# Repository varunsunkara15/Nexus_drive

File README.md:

# Nexus Drive

**Nexus Drive** is an open-hardware motor driver we are designing for a humanoid robot's joints.

The goal is a compact board that can sit near each joint actuator and drive its motor accurately and efficiently. It should also report back to the robot's main controller.

> **Status:** 🚧 Early development. Schematic in progress (power stage, gate driver, MCU, CAN-FD, encoders and sensing drawn; ERC has 0 errors; logic supplies, DC-link and input protection still to add); PCB layout not started.

---

## Repository layout

```
Nexus_drive/
├── hardware/                     KiCad 10 project (open nexus_drive.kicad_pro)
│   ├── nexus_drive.kicad_pro     Project file
│   ├── nexus_drive.kicad_sch     Root schematic sheet
│   ├── gate_driver.kicad_sch     DRV8353S gate driver and support parts
│   ├── h_bridge.kicad_sch        One half-bridge (MOSFETs, shunt, phase output), used 3× for phases A/B/C
│   ├── current_sense.kicad_sch   RC filters on the current-sense amplifier outputs
│   ├── stm32g474.kicad_sch       STM32G474METx MCU, wired to the pin plan
│   ├── can_fd.kicad_sch          TCAN1042GV CAN-FD transceiver and bus connectors
│   ├── encoders.kicad_sch        On-board MA702GQ encoder and external SPI encoder connectors
│   ├── sensing.kicad_sch         Bus and phase voltage dividers, FET and motor temperature inputs
│   ├── nexus_drive.kicad_sym     Project symbols (TCAN1042GV, MA702GQ, EMI filter)
│   ├── nexus_drive.kicad_pcb     PCB layout (not started)
│   ├── fp-lib-table, sym-lib-table   Project library tables
│   └── lib/                      Project-local symbol and footprint libraries (moteus)
├── firmware/
│   └── Comms Component Selection.ioc   STM32CubeMX pin assignment for the MCU
├── docs/
│   └── power-stage.md            Power stage design notes
├── LICENSES/, NOTICE.md          Attribution for files derived from mjbots moteus (Apache-2.0)
└── README.md
```

Folders for fabrication outputs (Gerbers, BOM, pick-and-place) and datasheets will be added as the design matures.

## Design goals

These are the intended targets. Values still marked **TBD** will be filled in as we choose parts. The power stage is described in detail in [docs/power-stage.md](docs/power-stage.md).

- **Motor type:** Brushless DC / PMSM motors used in humanoid joint actuators
- **Control:** Field-oriented control (FOC) for smooth, quiet torque control
- **Feedback:** Rotor position sensing (e.g. a magnetic encoder) and phase current sensing
- **Communication:** A bus to the robot's main controller, such as CAN / CAN-FD
- **Protection:** Over-current, over-voltage, under-voltage and over-temperature protection
- **Form factor:** Small enough to mount on or inside the joint actuator

### Planned specifications

| Parameter | Target |
| --- | --- |
| Battery | 12S3P Li-ion / LiPo: 36–50.4 V (44–48 V nominal) |
| Continuous / peak phase current | TBD (depends on the motor) |
| Microcontroller | STM32G474METx (LQFP-80, 170 MHz Cortex-M4) |
| Gate driver | TI DRV8353S (SPI-configured, integrated current-sense amplifiers) |
| MOSFETs | 6 × onsemi FDMT80080DC (80 V, 1.35 mΩ) |
| Current sensing | 3 low-side shunts (value TBD) |
| Overvoltage protection | Input TVS, bulk capacitor, 100 V ceramic DC-link bank, anti-spark connector |
| Encoder interface | 3 × SPI: on-board MA702GQ magnetic encoder, 2 external connectors |
| Communication | CAN-FD (TCAN1042GV), two daisy-chain connectors |
| Board dimensions | TBD |

### Note: bulk capacitance on the battery bus

The power stage in this repo has **no bulk / DC-link capacitor bank yet**. It is owned by another team member and must be added before the board is built. The reference design (moteus x1) uses 36 × 4.7 µF 100 V ceramics. A **bulk electrolytic (or tantalum) capacitor** at the power input may also be needed. Reasons:

- **Hot-plug ringing:** a bank of only ceramics has very low ESR. Together with the battery cable's inductance, it can ring up to ~2× the battery voltage when the battery is plugged in (~100 V on a 50.4 V pack), above the 80 V MOSFET rating. An electrolytic's higher ESR (≈ 0.05–0.1 Ω) damps this ringing.
- **Ceramics lose capacitance under DC bias:** 100 V X7R ceramics keep only about 30–50 % of their rated value at 50 V, so the real bus capacitance is much lower than the printed value.
- **Regen and load steps:** a larger capacitor absorbs some regenerative braking energy and supplies current during fast load changes, reducing bus voltage swings.

Guidance: rated **80 V or higher** (63 V is the bare minimum), capacitance several times the effective ceramic bank (e.g. 330–470 µF total), ESR ≈ 0.05–0.1 Ω, placed between the input connector and the half-bridges. **Tantalum is not recommended at this voltage:** tantalums need ~2× voltage derating (a >100 V part is hard to find), and they tend to fail short-circuit, which is a fire risk on a stiff 12S3P pack. Aluminium electrolytic or hybrid polymer is the safer choice. See [docs/power-stage.md](docs/power-stage.md) for the full overvoltage-protection requirements.

## Schematic review (3 Nov 2026)

This review covers the schematic and the first PCB placement at commit `5195f6f`: footprint assignment, the HC-05 header on J1, footprint import, and the `sensing` sheet. It was checked against the KiCad netlist, ERC and DRC. Blocks that are still to be drawn (logic supplies, DC-link, input protection) are planned work and are not reviewed.

**Design intent: the board is deliberately over-specified.** The first target motors are the CubeMars **RO80 KV105** (≈15 A rated, ~50 A peak) and **RO100 KV55** (≈20 A rated, ~62 A peak) at 48 V. The power stage keeps moteus x1's 120 A-class parts so that larger motors can be used later.

**Checks:** ERC has 0 errors and 9 library warnings. PCB-to-schematic parity has 0 issues.

### ✅ Done well
- **All 115 parts have footprints, and the packages match the parts:** LQFP-80 for the STM32G474ME, RTA-40 for the DRV8353SRTA, PQFN 8×8 for the FETs, QFN-16 3×3 for the MA702 and SOIC-8 for the TCAN1042.
- **J1 (HC-05) is crossed over correctly:** MCU TX (PB10) goes to the module's RXD, and MCU RX (PE15) to its TXD.
- **The sensing sheet is well thought out:**
  - The VBUS divider (99.8k / 4.7k) gives 2.27 V at 50.4 V and reaches 3.3 V full scale at about 73 V, so it can see regen overvoltage.
  - The top resistor is split into two, so each 0603 sees only about 25 V.
  - The three phase-voltage dividers use the same ratio, filtered at about 3.5 kHz.
  - The thermistors have 1 % pull-ups and filter caps, and every signal goes to an ADC pin.
- Carried over from earlier work:
  - The power stage is copied from moteus x1 pin for pin.
  - DRV8353 nFAULT goes to TIM1_BKIN, so a driver fault stops PWM in hardware.
  - Each phase current has its own ADC.
  - CAN-FD has a choke, ESD protection and jumper-selectable termination.
  - Encoders have ESD protection and series resistors.

### 🔴 Fix before routing
- [ ] **N1: the VGLS capacitor C23 returns to `GND`.** VGLS supplies the low-side gate drive, so C23 must return to **`GNDPWR` at the DRV8353 PGND pin**. On `GND`, the gate current crosses between the two grounds every PWM cycle.
- [ ] **N2: `GND` and `GNDPWR` aren't joined anywhere.** NT1 joins only `GNDA` to `GND`, and NT3/5/7 are the shunt sense connections, so they don't count. Add **one net tie under the driver**.
- [ ] **N3: check FL1's pin numbers against the TDK ACT1210D datasheet.** The symbol uses windings 1–4 and 2–3. If TDK numbers them differently, the choke either shorts CANH to CANL or breaks the CAN line. Check the land pattern at the same time. Neither has been verified yet.
- [ ] **N4: placement has started before the parts that set the layout exist.** The DC-link capacitors, input connector and protection, and the logic supplies (+12 V, +5 V, +3.3 V) aren't drawn yet. Those decide where the power stage, the ground tie and the heat paths go. Finish them, plus N5, before placing parts seriously.

### 🟠 Should fix
- [ ] **N5: VM bulk capacitance.** +12 V (the DRV8353 VM pin) has only 0.1 µF (C19). Add the local bulk capacitor the DRV8353 datasheet recommends, next to the pin.
- [ ] **N6: drill size on the phase output pads.** X1–X3 each have 20 vias with 0.254 mm holes, but the board rule minimum is 0.3 mm, giving 60 DRC errors. Either confirm the fab can drill 0.25 mm and change the rule, or enlarge the holes to 0.3 mm. These vias carry phase current, so their size and count matter for the over-spec rating (N13).
- [ ] **N7: protect the motor thermistor input.** J7 leaves the board next to the phase wires and goes straight to the ADC with only 100 nF. Add about 1k in series and an ESD clamp. A motor thermistor sits inside the windings, so an insulation fault can put bus voltage on that ADC pin.
- [ ] **N8: HC-05 on J1.**
  - Nothing supplies `+5V` yet. Include the HC-05 (up to about 40 mA while pairing) and the TCAN1042 (about 70 mA) in the 5 V budget.
  - J1 is a male pin header and the HC-05 module also has male pins, so it needs a cable or a socket.
  - Treat Bluetooth as a bench and debug link only. CAN is the main bus for 12 joints.
- [ ] **N9: current-sense gain must be set per motor.** With the 0.5 mΩ shunts, gain 40 gives ±70 A full scale, for the RO80 and RO100. Gain 20 gives ±140 A, for larger motors. Make the gain a per-motor firmware parameter.
- [ ] **N10: gate-drive supply versus PWM frequency.** Six FDMT80080DC gates (195 nC each) at 30 kHz need about 35 mA. Check that against the DRV8353 charge-pump and VGLS limits before fixing the PWM frequency, and include it in the +12 V budget.
- [ ] **N11: sensing offset and ratiometric reference.** The current-sense amplifier zero (VREF/2) and the thermistor pull-ups run from `+3V`, but the ADC reference is `+3VA`. Calibrate the offsets at startup with the gates off, or move them to `+3VA`.
- [ ] **N12: external encoders.**
  - J903/J904 take power from the MCU's own `+3V`, so a shorted encoder cable resets the MCU. Add a polyfuse, a load switch or a separate LDO.
  - Keep single-ended SPI cables short and slow, or use RS-485/SSI for the joint-output encoder.
- [ ] **N13: thermal design for the over-spec rating.** The 120 A-class headroom only holds with:
  - heavy copper for V+, the phases and `GNDPWR`
  - a thermal path for the Dual Cool FETs
  - shunts sized for the largest motor you plan to use

### 🟡 Housekeeping
- [ ] **N14:** `sym-lib-table` has no `nexus_drive` entry, which causes 3 ERC warnings.
- [ ] **N15:** The U6 footprint differs from the library copy. Update it from the library, or note why it's custom.
- [ ] **N16:** Before routing, add the board outline. The 196 silkscreen warnings from placement can be cleaned up later.
- [ ] **N17:** Check the following:
  - The SWD header order (VCC, SWDIO, SWCLK, NRST, GND) isn't a standard pinout. Match it to your programmer.
  - The 12 pF crystal caps should suit the 16 MHz crystal's load capacitance.
  - PD10 (DRV chip select) has no label in the `.ioc`.
- [ ] **N18:** Consider split CAN termination (2 × 60 Ω + ~4.7 nF to GND) for better EMC on a long robot bus.
- [ ] **N19:** Commit the literature review (moteus, ODrive, ODESC, ODRI) to `docs/`.

**Most important:** N1, N2 and N4. Get the grounding and the missing power blocks into the schematic before routing.

## Getting started

### Requirements

- [KiCad](https://www.kicad.org/) **10.0** or newer. The project files use the KiCad 10 format and will not open in older versions.

### Opening the project

```bash
git clone https://github.com/varunsunkara15/Nexus_drive.git
cd Nexus_drive
```

Then open `hardware/nexus_drive.kicad_pro` in KiCad.

## Roadmap

- [x] Create the KiCad project and repository
- [ ] Define the specifications (battery voltage ✅, motor current, motor type)
- [ ] Choose the main parts (gate driver ✅, MOSFETs ✅, MCU ✅, shunts, encoder)
- [ ] Draw the schematic (phase power section ✅, gate driver ✅, MCU pin connections ✅, CAN-FD ✅, encoders ✅, sensing ✅, logic supplies, DC-link, input protection)
- [ ] Lay out the PCB
- [ ] Run design review, DRC and ERC
- [ ] Order and assemble the first prototype
- [ ] Bring up the board and write the firmware (FOC loop, communication)
- [ ] Test on a humanoid joint actuator

## Contributing

This project is under active development. Issues and pull requests are welcome. Please describe the change you're proposing, and why, before sending large design changes.

## License

No license has been chosen yet. Until one is added, all rights are reserved by the authors.

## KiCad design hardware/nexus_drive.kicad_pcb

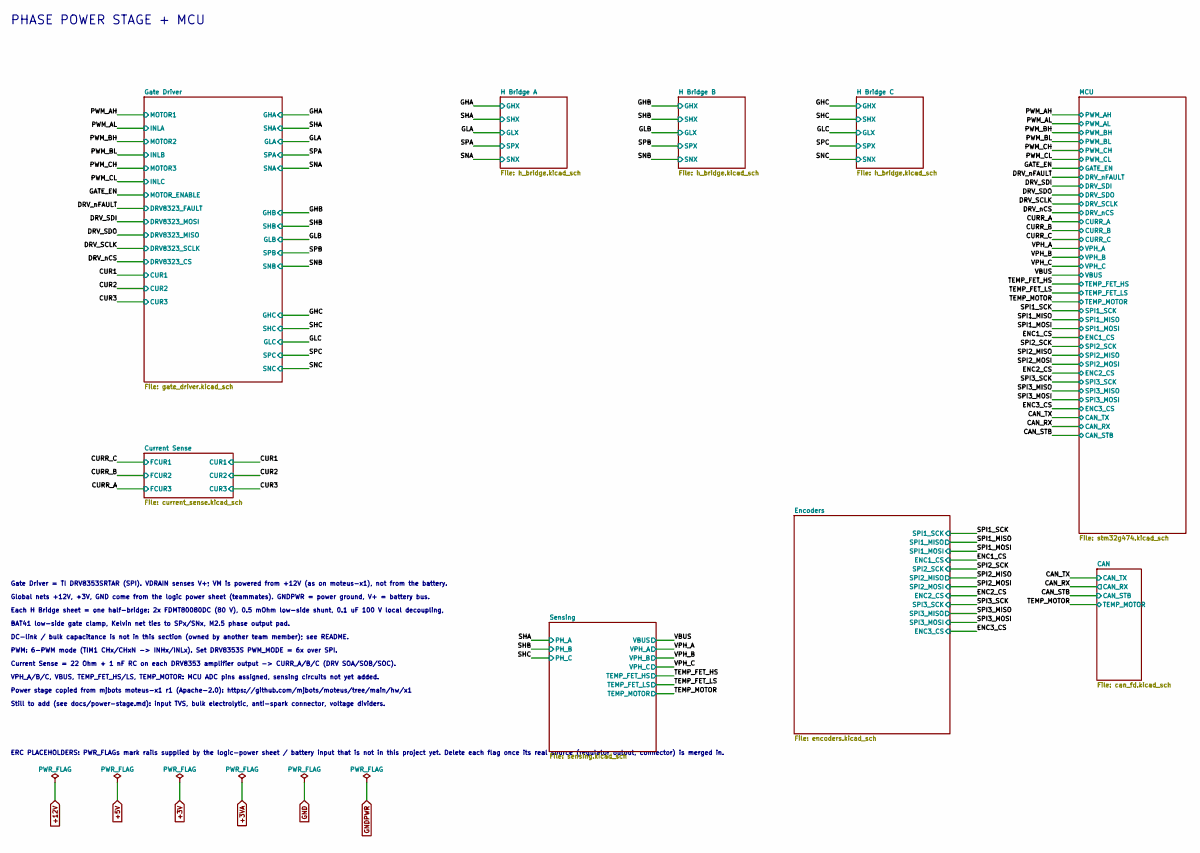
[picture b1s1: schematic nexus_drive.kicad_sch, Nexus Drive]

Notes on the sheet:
PWM: 6-PWM mode (TIM1 CHx/CHxN -> INHx/INLx). Set DRV8353S PWM_MODE = 6x over SPI.
Each H Bridge sheet = one half-bridge: 2x FDMT80080DC (80 V), 0.5 mOhm low-side shunt, 0.1 uF 100 V local decoupling,
Global nets +12V, +3V, GND come from the logic power sheet (teammates). GNDPWR = power ground, V+ = battery bus.
Gate Driver = TI DRV8353SRTAR (SPI). VDRAIN senses V+; VM is powered from +12V (as on moteus-x1), not from the battery.
DC-link / bulk capacitance is not in this section (owned by another team member); see README.
BAT41 low-side gate clamp, Kelvin net ties to SPx/SNx, M2.5 phase output pad.
Power stage copied from mjbots moteus-x1 r1 (Apache-2.0): https://github.com/mjbots/moteus/tree/main/hw/x1
Current Sense = 22 Ohm + 1 nF RC on each DRV8353 amplifier output -> CURR_A/B/C (DRV SOA/SOB/SOC).
ERC PLACEHOLDERS: PWR_FLAGs mark rails supplied by the logic-power sheet / battery input that is not in this project yet. Delete each flag once its real source (regulator output, connector) is merged in.
PHASE POWER STAGE + MCU
VPH_A/B/C, VBUS, TEMP_FET_HS/LS, TEMP_MOTOR: MCU ADC pins assigned, sensing circuits not yet added.
Still to add (see docs/power-stage.md): input TVS, bulk electrolytic, anti-spark connector, voltage dividers.

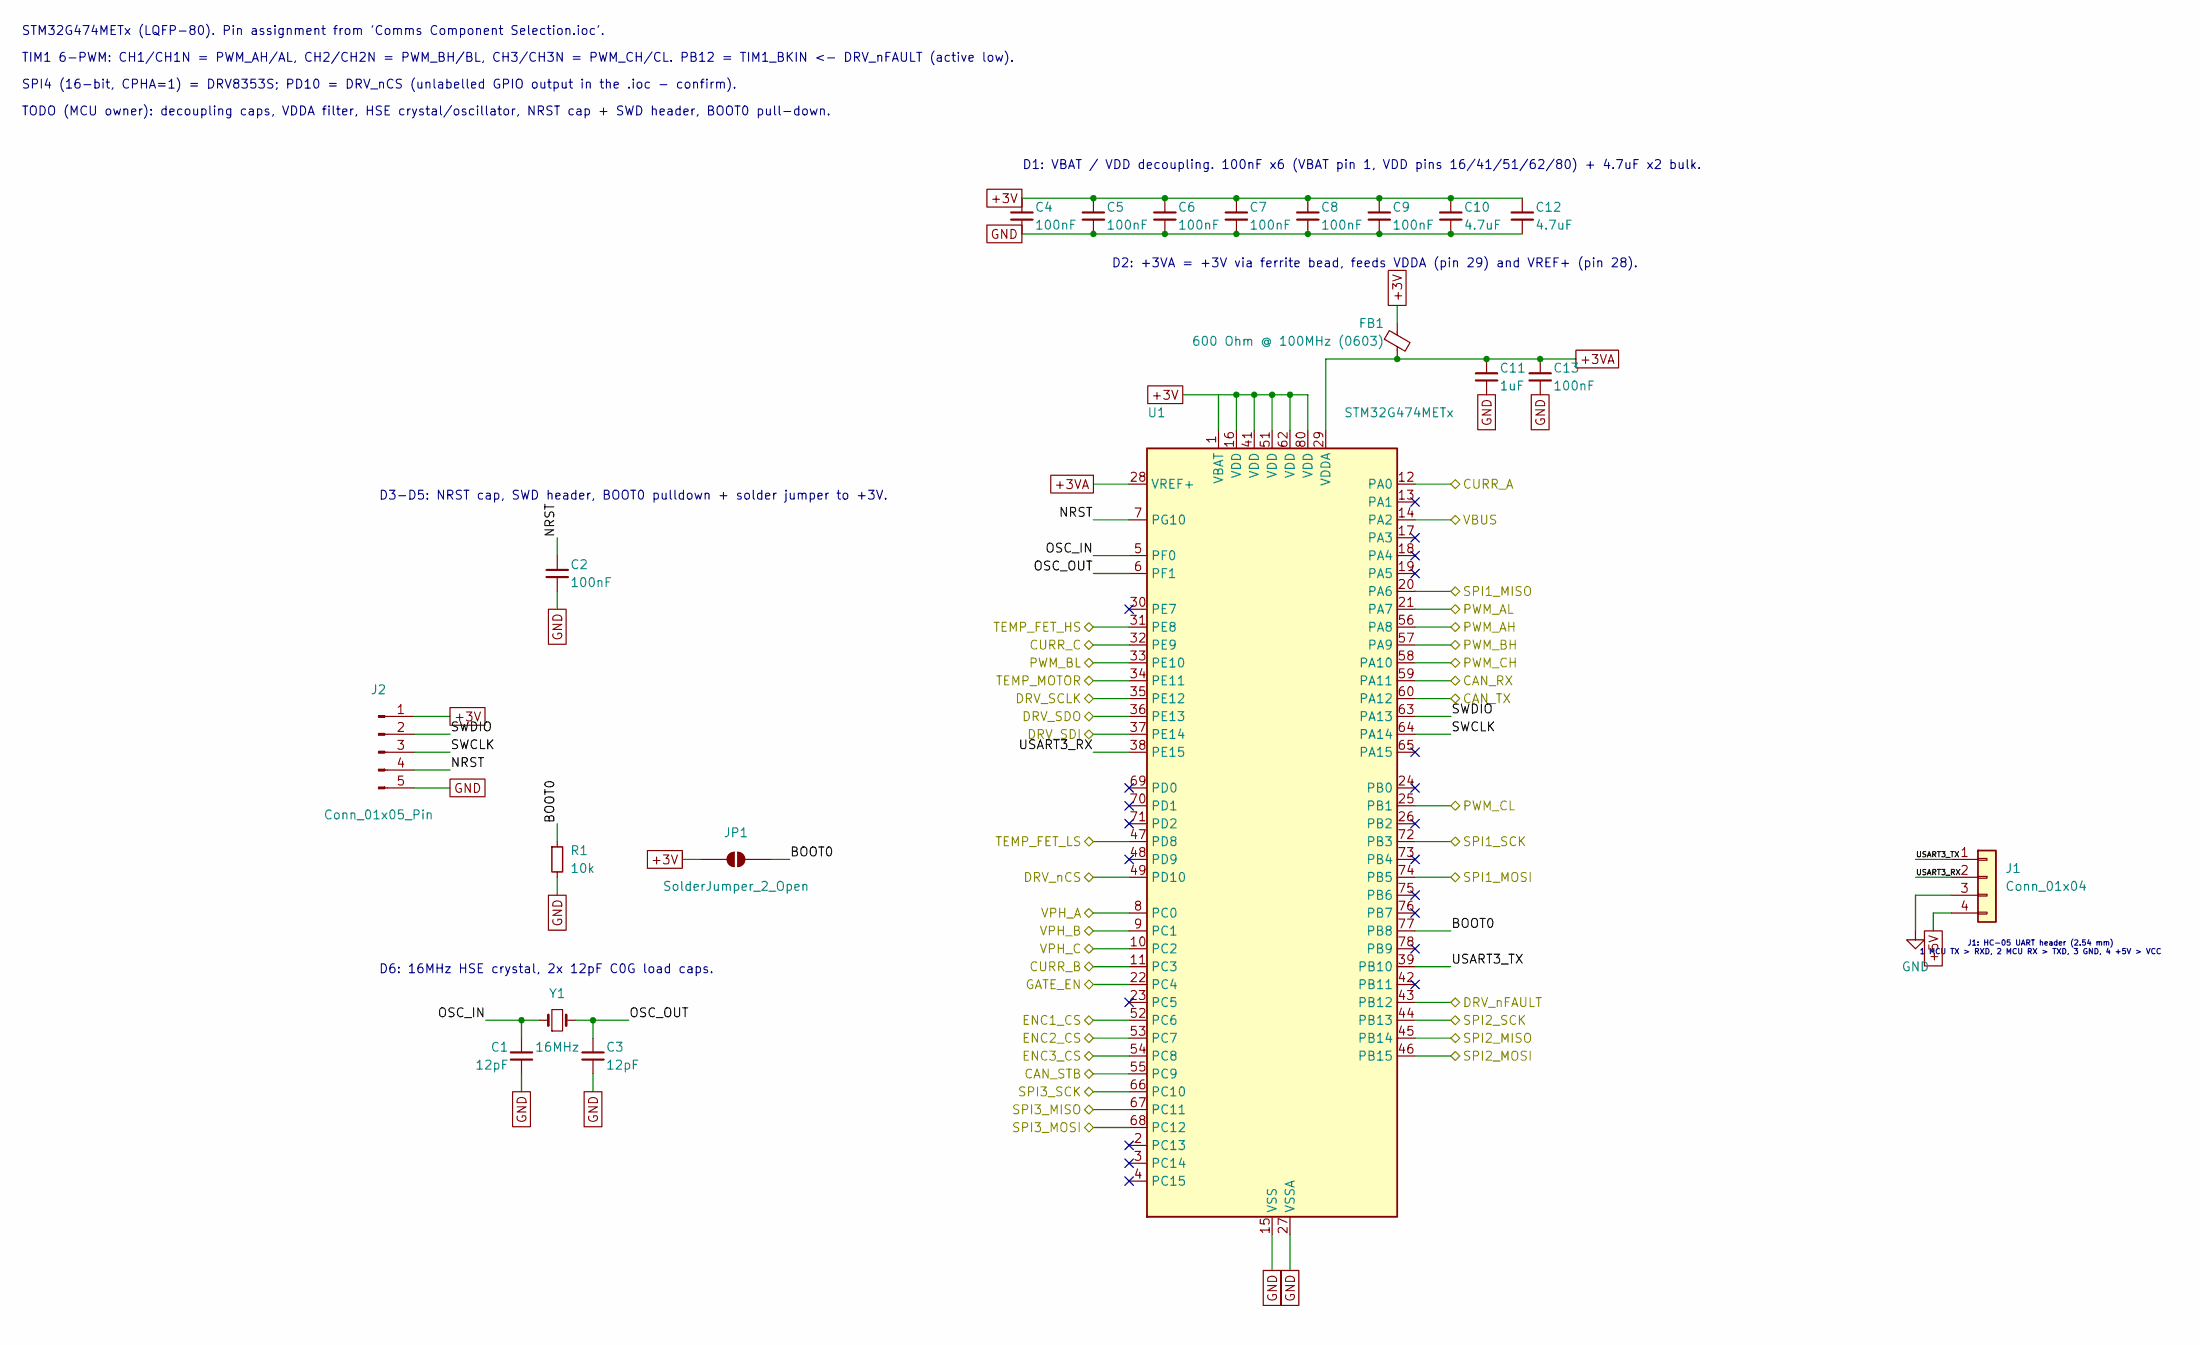
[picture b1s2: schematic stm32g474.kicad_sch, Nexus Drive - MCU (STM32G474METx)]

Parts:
C1, C3: 12pF; C_0603_1608Metric
C2, C4, C5, C6, C7, C8, C9, C13: 100nF; C_0603_1608Metric
C10, C12: 4.7uF; C_0805_2012Metric
C11: 1uF; C_0603_1608Metric
FB1: 600 Ohm @ 100MHz (0603); L_0603_1608Metric
J1: Conn_01x04; PinHeader_1x04_P2.54mm_Vertical
J2: Conn_01x05_Pin; PinHeader_1x05_P1.27mm_Vertical
JP1: SolderJumper_2_Open; SolderJumper-2_P1.3mm_Open_Pad1.0x1.5mm
R1: 10k; R_0603_1608Metric
U1: STM32G474METx; LQFP-80_12x12mm_P0.5mm
Y1: 16MHz; Crystal_SMD_5032-2Pin_5.0x3.2mm; MPN ABM8-16.000MHZ-10-1-U-T

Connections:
+3V: C4.1, C5.1, C6.1, C7.1, C8.1, C9.1, C10.1, C12.1, FB1.1, J2.1, JP1.1 (A), U1.1 (VBAT), U1.16 (VDD), U1.41 (VDD), U1.51 (VDD), U1.62 (VDD), U1.80 (VDD); also elsewhere on the board
+3VA: C11.1, C13.1, FB1.2, U1.28 (VREF+), U1.29 (VDDA); also elsewhere on the board
+5V: J1.4; also elsewhere on the board
/CAN_RX: U1.59 (PA11); also elsewhere on the board
/CAN_STB: U1.55 (PC9); also elsewhere on the board
/CAN_TX: U1.60 (PA12); also elsewhere on the board
/CURR_A: U1.12 (PA0); also elsewhere on the board
/CURR_B: U1.11 (PC3); also elsewhere on the board
/CURR_C: U1.32 (PE9); also elsewhere on the board
/DRV_SCLK: U1.35 (PE12); also elsewhere on the board
/DRV_SDI: U1.37 (PE14); also elsewhere on the board
/DRV_SDO: U1.36 (PE13); also elsewhere on the board
/DRV_nCS: U1.49 (PD10); also elsewhere on the board
/DRV_nFAULT: U1.43 (PB12); also elsewhere on the board
/ENC1_CS: U1.52 (PC6); also elsewhere on the board
/ENC2_CS: U1.53 (PC7); also elsewhere on the board
/ENC3_CS: U1.54 (PC8); also elsewhere on the board
/GATE_EN: U1.22 (PC4); also elsewhere on the board
/MCU/BOOT0: JP1.2 (B), R1.1, U1.77 (PB8)
/MCU/NRST: C2.1, J2.4, U1.7 (PG10)
/MCU/OSC_IN: C1.1, U1.5 (PF0), Y1.1
/MCU/OSC_OUT: C3.1, U1.6 (PF1), Y1.2
/MCU/SWCLK: J2.3, U1.64 (PA14)
/MCU/SWDIO: J2.2, U1.63 (PA13)
/MCU/USART3_RX: J1.2, U1.38 (PE15)
/MCU/USART3_TX: J1.1, U1.39 (PB10)
/PWM_AH: U1.56 (PA8); also elsewhere on the board
/PWM_AL: U1.21 (PA7); also elsewhere on the board
/PWM_BH: U1.57 (PA9); also elsewhere on the board
/PWM_BL: U1.33 (PE10); also elsewhere on the board
/PWM_CH: U1.58 (PA10); also elsewhere on the board
/PWM_CL: U1.25 (PB1); also elsewhere on the board
/SPI1_MISO: U1.20 (PA6); also elsewhere on the board
/SPI1_MOSI: U1.74 (PB5); also elsewhere on the board
/SPI1_SCK: U1.72 (PB3); also elsewhere on the board
/SPI2_MISO: U1.45 (PB14); also elsewhere on the board
/SPI2_MOSI: U1.46 (PB15); also elsewhere on the board
/SPI2_SCK: U1.44 (PB13); also elsewhere on the board
/SPI3_MISO: U1.67 (PC11); also elsewhere on the board
/SPI3_MOSI: U1.68 (PC12); also elsewhere on the board
/SPI3_SCK: U1.66 (PC10); also elsewhere on the board
/TEMP_FET_HS: U1.31 (PE8); also elsewhere on the board
/TEMP_FET_LS: U1.47 (PD8); also elsewhere on the board
/TEMP_MOTOR: U1.34 (PE11); also elsewhere on the board
/VBUS: U1.14 (PA2); also elsewhere on the board
/VPH_A: U1.8 (PC0); also elsewhere on the board
/VPH_B: U1.9 (PC1); also elsewhere on the board
/VPH_C: U1.10 (PC2); also elsewhere on the board
GND: C1.2, C2.2, C3.2, C4.2, C5.2, C6.2, C7.2, C8.2, C9.2, C10.2, C11.2, C12.2, C13.2, J1.3, J2.5, R1.2, U1.15 (VSS), U1.27 (VSSA), U1.40 (VSS), U1.50 (VSS), U1.61 (VSS), U1.79 (VSS); also elsewhere on the board

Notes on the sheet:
D2: +3VA = +3V via ferrite bead, feeds VDDA (pin 29) and VREF+ (pin 28).
J1: HC-05 UART header (2.54 mm) 1 MCU TX > RXD, 2 MCU RX > TXD, 3 GND, 4 +5V > VCC
TODO (MCU owner): decoupling caps, VDDA filter, HSE crystal/oscillator, NRST cap + SWD header, BOOT0 pull-down.
SPI4 (16-bit, CPHA=1) = DRV8353S; PD10 = DRV_nCS (unlabelled GPIO output in the .ioc - confirm).
D1: VBAT / VDD decoupling. 100nF x6 (VBAT pin 1, VDD pins 16/41/51/62/80) + 4.7uF x2 bulk.
D6: 16MHz HSE crystal, 2x 12pF C0G load caps.
STM32G474METx (LQFP-80). Pin assignment from 'Comms Component Selection.ioc'.
TIM1 6-PWM: CH1/CH1N = PWM_AH/AL, CH2/CH2N = PWM_BH/BL, CH3/CH3N = PWM_CH/CL. PB12 = TIM1_BKIN <- DRV_nFAULT (active low).
D3-D5: NRST cap, SWD header, BOOT0 pulldown + solder jumper to +3V.

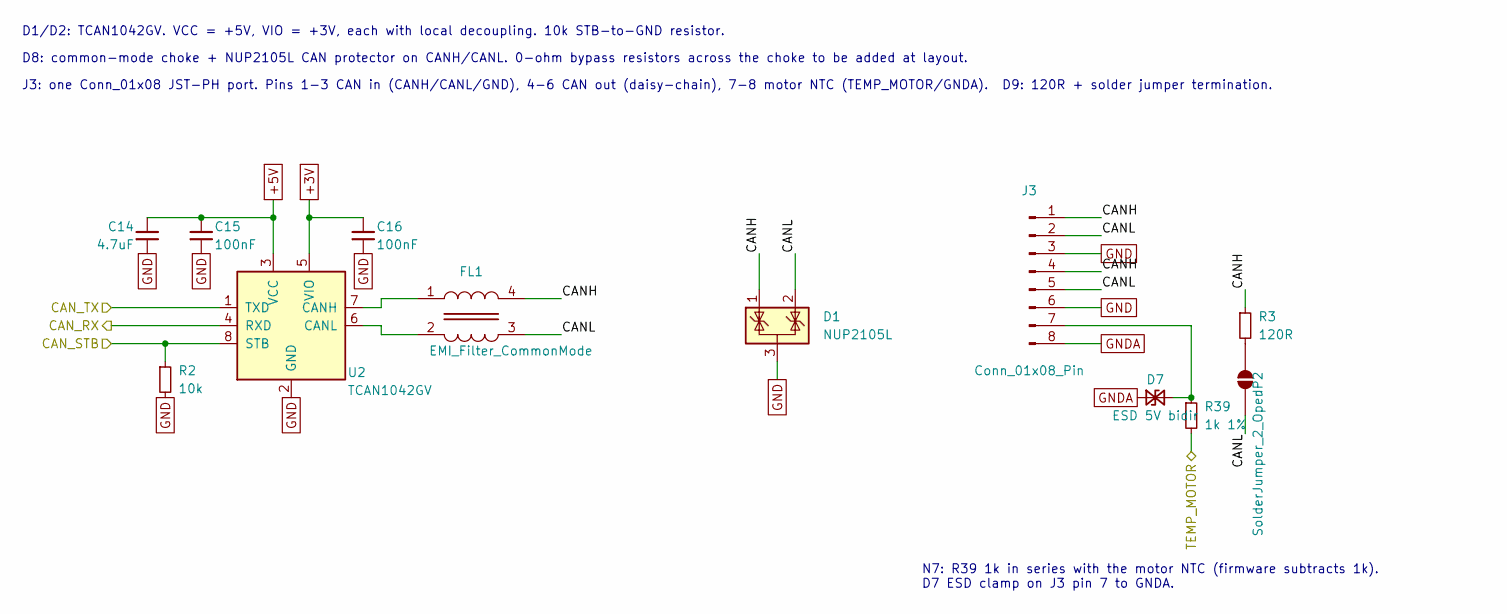
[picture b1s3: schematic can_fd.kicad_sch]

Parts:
C14: 4.7uF; C_0805_2012Metric
C15, C16: 100nF; C_0603_1608Metric
D1: NUP2105L; SOT-23
D7: ESD 5V bidir; D_SOD-323
FL1: EMI_Filter_CommonMode; L_CommonMode_TDK_ACT1210D
J3: Conn_01x08_Pin; JST_PH_B8B-PH-K_1x08_P2.00mm_Vertical
JP2: SolderJumper_2_Open; SolderJumper-2_P1.3mm_Open_Pad1.0x1.5mm
R2: 10k; R_0603_1608Metric
R3: 120R; R_0603_1608Metric
R39: 1k 1%; R_0603_1608Metric
U2: TCAN1042GV; SOIC-8_3.9x4.9mm_P1.27mm

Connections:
+3V: C16.1, U2.5 (VIO); also elsewhere on the board
+5V: C14.1, C15.1, U2.3 (VCC); also elsewhere on the board
/CAN/CANH: D1.1 (K), FL1.4, J3.1, J3.4, R3.1
/CAN/CANL: D1.2 (K), FL1.3, J3.2, J3.5, JP2.2 (B)
/CAN_RX: U2.4 (RXD); also elsewhere on the board
/CAN_STB: R2.1, U2.8 (STB); also elsewhere on the board
/CAN_TX: U2.1 (TXD); also elsewhere on the board
/TEMP_MOTOR: R39.2; also elsewhere on the board
GND: C14.2, C15.2, C16.2, D1.3 (A), J3.3, J3.6, R2.2, U2.2 (GND); also elsewhere on the board
GNDA: D7.1 (A1), J3.8; also elsewhere on the board
unnamed: D7.2 (A2), J3.7, R39.1
unnamed: JP2.1 (A), R3.2
unnamed: FL1.1, U2.7 (CANH)
unnamed: FL1.2, U2.6 (CANL)

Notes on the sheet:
D8: common-mode choke + NUP2105L CAN protector on CANH/CANL. 0-ohm bypass resistors across the choke to be added at layout.
D1/D2: TCAN1042GV. VCC = +5V, VIO = +3V, each with local decoupling. 10k STB-to-GND resistor.
J3: one Conn_01x08 JST-PH port. Pins 1-3 CAN in (CANH/CANL/GND), 4-6 CAN out (daisy-chain), 7-8 motor NTC (TEMP_MOTOR/GNDA). D9: 120R + solder jumper termination.
N7: R39 1k in series with the motor NTC (firmware subtracts 1k). D7 ESD clamp on J3 pin 7 to GNDA.

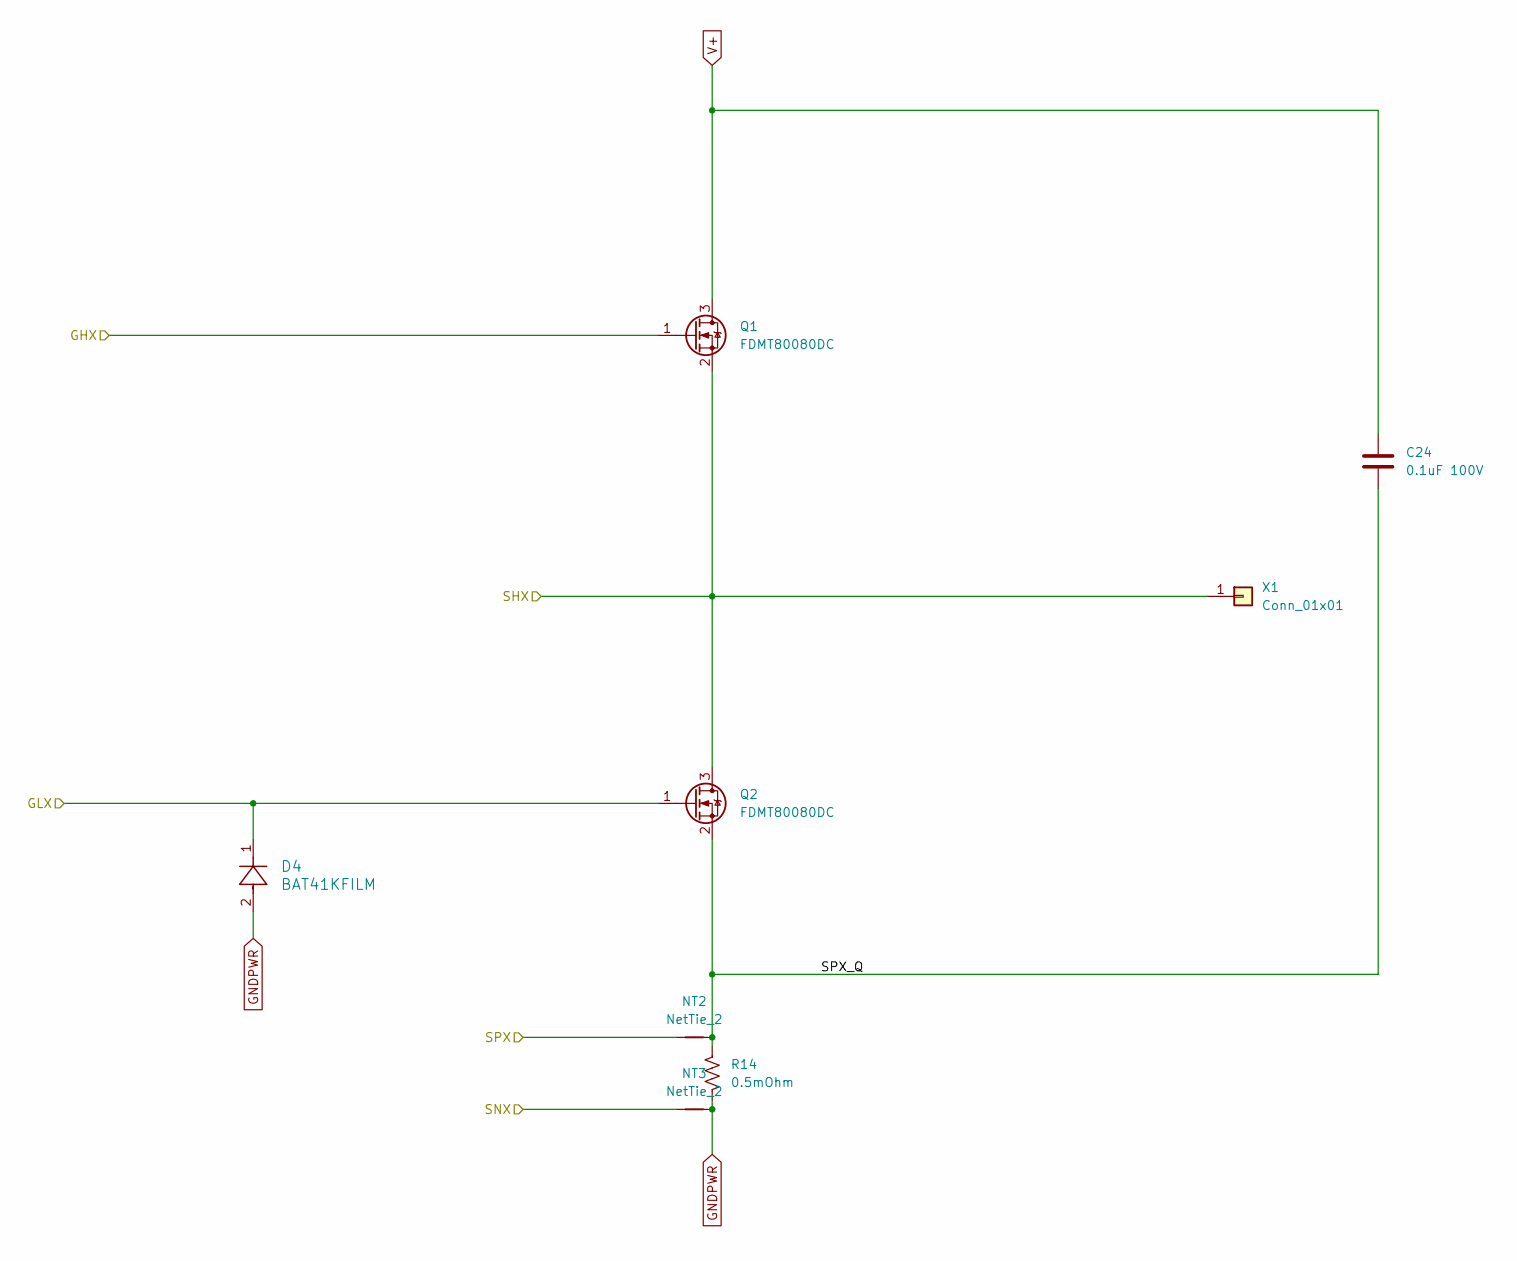
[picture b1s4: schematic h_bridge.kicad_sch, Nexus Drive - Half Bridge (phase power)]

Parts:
C24: 0.1uF 100V; C_1812_4532Metric; MPN 18121C104MAT2A
D4: BAT41KFILM; SOD-523_STM; MPN BAT41KFILM
NT2, NT3: NetTie_2; NetTie-2_SMD_Pad0.2
Q1, Q2: FDMT80080DC; PQFN_8x8; MPN FDMT80080DC
R14: 0.5mOhm; R_2512_6332Metric; MPN WSLF2512L5000FEA
X1: Conn_01x01; POWER_M2.5

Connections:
/GHA: Q1.1 (G); also elsewhere on the board
/GLA: D4.1, Q2.1 (G); also elsewhere on the board
/H Bridge A/SPX_Q: C24.2, NT2.2, Q2.2 (S), R14.1
/SHA: Q1.2 (S), Q2.3 (D), X1.1 (Pin_1_1); also elsewhere on the board
/SNA: NT3.1; also elsewhere on the board
/SPA: NT2.1; also elsewhere on the board
GNDPWR: D4.2, NT3.2, R14.2; also elsewhere on the board
V+: C24.1, Q1.3 (D); also elsewhere on the board

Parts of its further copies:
C25, C26: 0.1uF 100V; C_1812_4532Metric; MPN 18121C104MAT2A
D5, D6: BAT41KFILM; SOD-523_STM; MPN BAT41KFILM
NT4, NT5, NT6, NT7: NetTie_2; NetTie-2_SMD_Pad0.2
Q3, Q4, Q5, Q6: FDMT80080DC; PQFN_8x8; MPN FDMT80080DC
R15, R16: 0.5mOhm; R_2512_6332Metric; MPN WSLF2512L5000FEA
X2, X3: Conn_01x01; POWER_M2.5

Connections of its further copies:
/GHB: Q3.1 (G); also elsewhere on the board
/GHC: Q5.1 (G); also elsewhere on the board
/GLB: D5.1, Q4.1 (G); also elsewhere on the board
/GLC: D6.1, Q6.1 (G); also elsewhere on the board
/H Bridge B/SPX_Q: C25.2, NT4.2, Q4.2 (S), R15.1
/H Bridge C/SPX_Q: C26.2, NT6.2, Q6.2 (S), R16.1
/SHB: Q3.2 (S), Q4.3 (D), X2.1 (Pin_1_1); also elsewhere on the board
/SHC: Q5.2 (S), Q6.3 (D), X3.1 (Pin_1_1); also elsewhere on the board
/SNB: NT5.1; also elsewhere on the board
/SNC: NT7.1; also elsewhere on the board
/SPB: NT4.1; also elsewhere on the board
/SPC: NT6.1; also elsewhere on the board
GNDPWR: D5.2, D6.2, NT5.2, NT7.2, R15.2, R16.2; also elsewhere on the board
V+: C25.1, C26.1, Q3.3 (D), Q5.3 (D); also elsewhere on the board

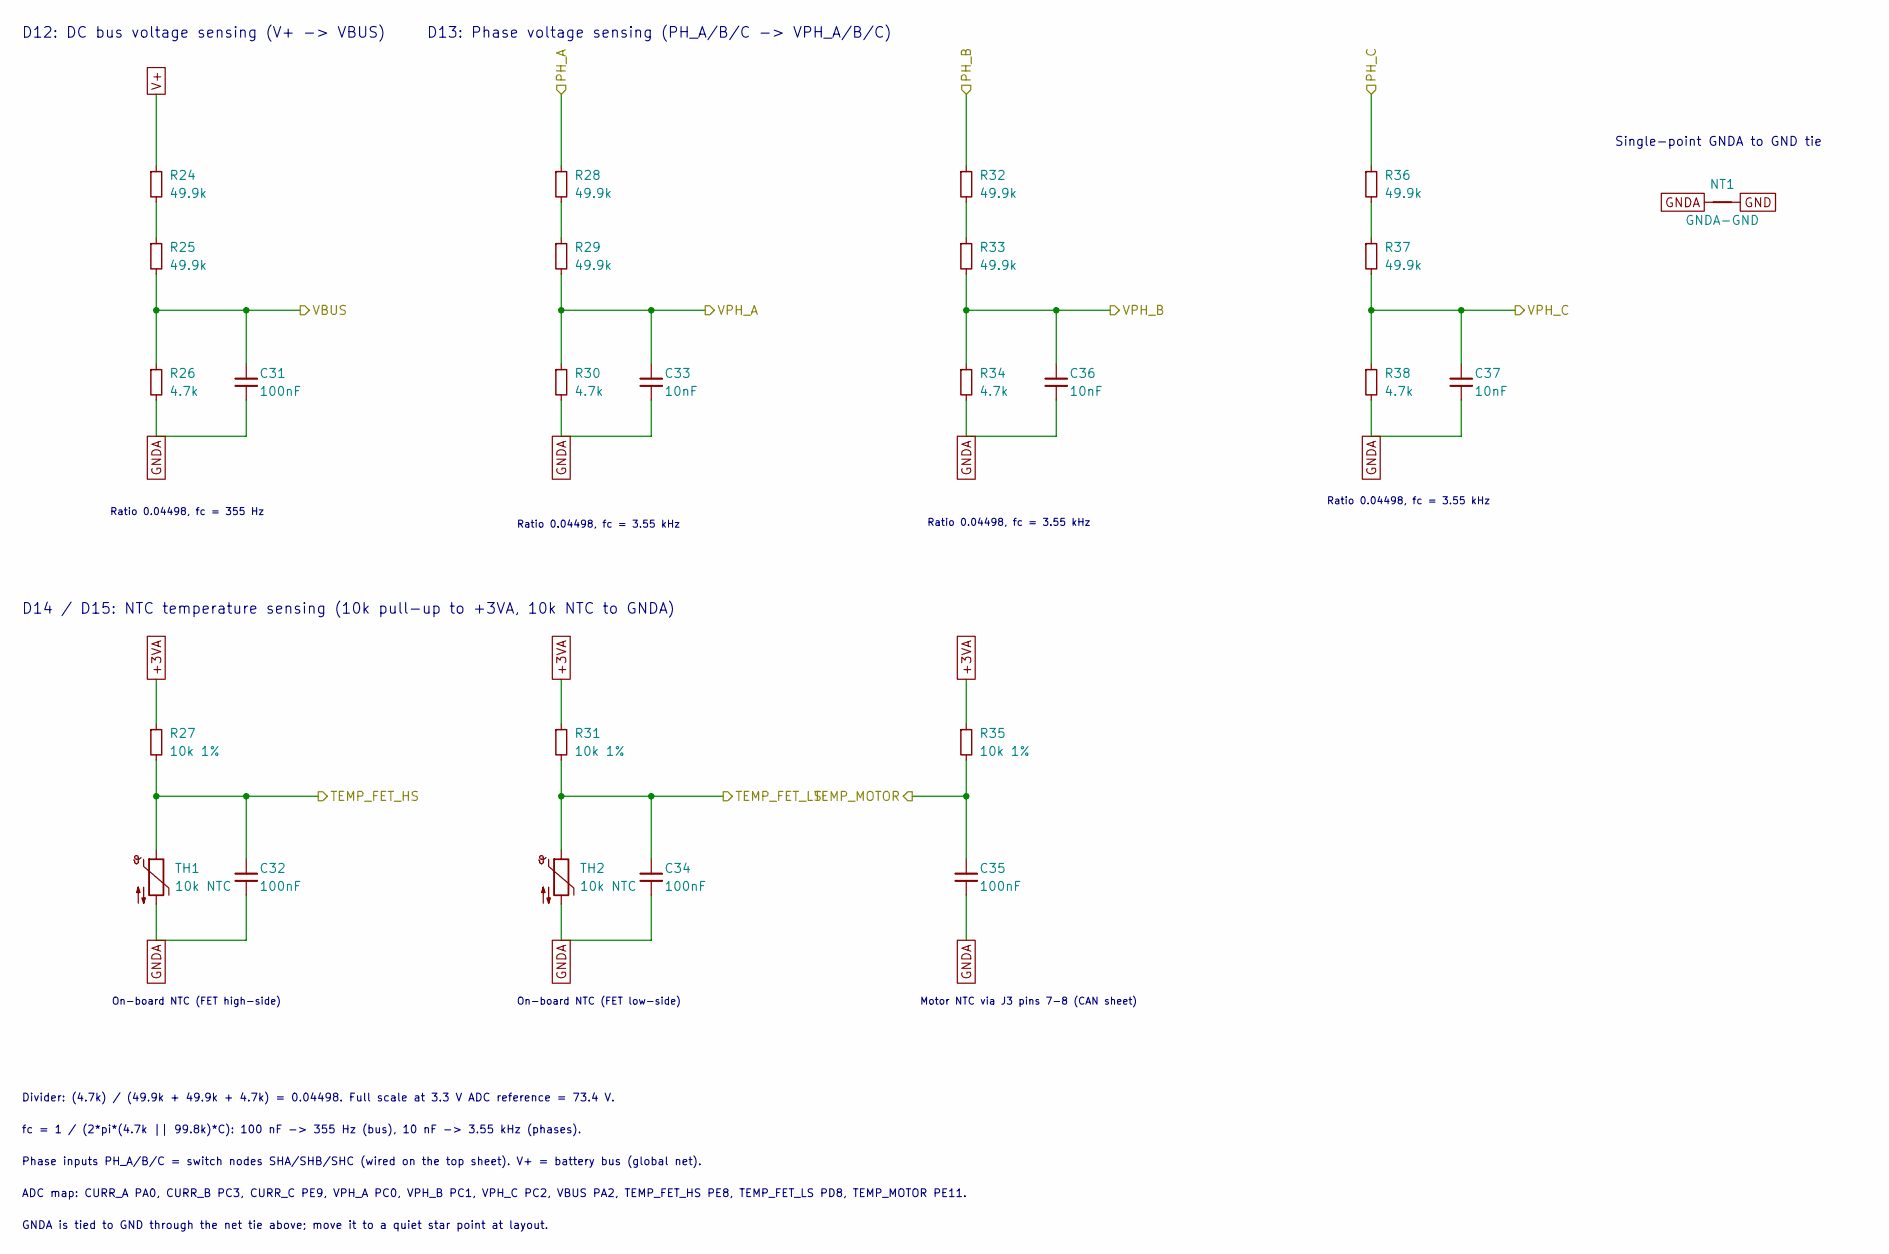
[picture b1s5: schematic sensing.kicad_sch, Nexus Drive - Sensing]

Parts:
C31, C32, C34, C35: 100nF; C_0603_1608Metric
C33, C36, C37: 10nF; C_0603_1608Metric
NT1: GNDA-GND; NetTie-2_SMD_Pad0.5mm
R24, R25, R28, R29, R32, R33, R36, R37: 49.9k; R_0805_2012Metric
R26, R30, R34, R38: 4.7k; R_0603_1608Metric
R27, R31, R35: 10k 1%; R_0603_1608Metric
TH1, TH2: 10k NTC; R_0603_1608Metric

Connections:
+3VA: R27.1, R31.1, R35.1; also elsewhere on the board
/SHA: R28.1; also elsewhere on the board
/SHB: R32.1; also elsewhere on the board
/SHC: R36.1; also elsewhere on the board
/TEMP_FET_HS: C32.1, R27.2, TH1.1; also elsewhere on the board
/TEMP_FET_LS: C34.1, R31.2, TH2.1; also elsewhere on the board
/TEMP_MOTOR: C35.1, R35.2; also elsewhere on the board
/VBUS: C31.1, R25.2, R26.1; also elsewhere on the board
/VPH_A: C33.1, R29.2, R30.1; also elsewhere on the board
/VPH_B: C36.1, R33.2, R34.1; also elsewhere on the board
/VPH_C: C37.1, R37.2, R38.1; also elsewhere on the board
GND: NT1.2; also elsewhere on the board
GNDA: C31.2, C32.2, C33.2, C34.2, C35.2, C36.2, C37.2, NT1.1, R26.2, R30.2, R34.2, R38.2, TH1.2, TH2.2; also elsewhere on the board
unnamed: R24.2, R25.1
unnamed: R28.2, R29.1
unnamed: R32.2, R33.1
unnamed: R36.2, R37.1
V+: R24.1; also elsewhere on the board

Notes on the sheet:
Phase inputs PH_A/B/C = switch nodes SHA/SHB/SHC (wired on the top sheet). V+ = battery bus (global net).
Ratio 0.04498, fc = 355 Hz
Motor NTC via J3 pins 7-8 (CAN sheet)
D14 / D15: NTC temperature sensing (10k pull-up to +3VA, 10k NTC to GNDA)
On-board NTC (FET high-side)
Ratio 0.04498, fc = 3.55 kHz
GNDA is tied to GND through the net tie above; move it to a quiet star point at layout.
Single-point GNDA to GND tie
D12: DC bus voltage sensing (V+ -> VBUS)
D13: Phase voltage sensing (PH_A/B/C -> VPH_A/B/C)
ADC map: CURR_A PA0, CURR_B PC3, CURR_C PE9, VPH_A PC0, VPH_B PC1, VPH_C PC2, VBUS PA2, TEMP_FET_HS PE8, TEMP_FET_LS PD8, TEMP_MOTOR PE11.
Divider: (4.7k) / (49.9k + 49.9k + 4.7k) = 0.04498. Full scale at 3.3 V ADC reference = 73.4 V.
On-board NTC (FET low-side)
fc = 1 / (2*pi*(4.7k || 99.8k)*C): 100 nF -> 355 Hz (bus), 10 nF -> 3.55 kHz (phases).

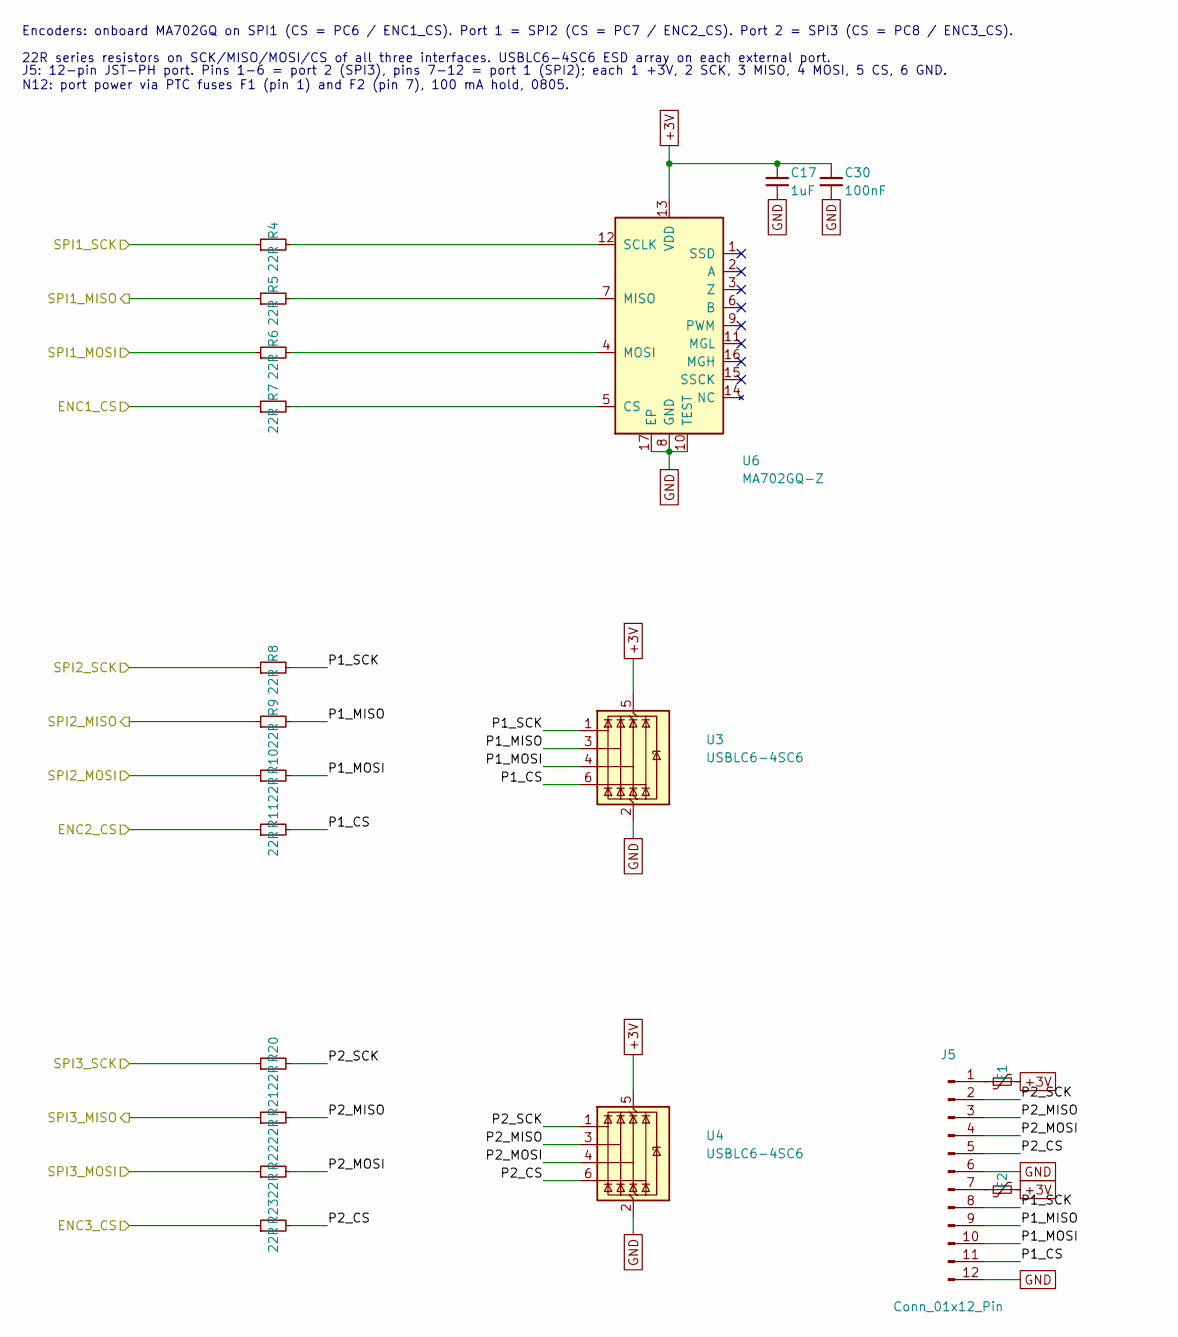
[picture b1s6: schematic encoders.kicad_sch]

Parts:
C17: 1uF; C_0603_1608Metric
C30: 100nF; C_0603_1608Metric
F1, F2: PTC 100mA hold; Fuse_0805_2012Metric
J5: Conn_01x12_Pin; JST_PH_B12B-PH-K_1x12_P2.00mm_Vertical
R4, R5, R6, R7, R8, R9, R10, R11, R20, R21, R22, R23: 22R; R_0603_1608Metric
U3, U4: USBLC6-4SC6; SOT-23-6
U6: MA702GQ-Z; QFN-16-1EP_3x3mm_P0.5mm_EP1.7x1.7mm

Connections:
+3V: C17.1, C30.1, F1.2, F2.2, U3.5 (VBUS), U4.5 (VBUS), U6.13 (VDD); also elsewhere on the board
/ENC1_CS: R7.1; also elsewhere on the board
/ENC2_CS: R11.1; also elsewhere on the board
/ENC3_CS: R23.1; also elsewhere on the board
/Encoders/P1_CS: J5.11, R11.2, U3.6 (I/O4)
/Encoders/P1_MISO: J5.9, R9.2, U3.3 (I/O2)
/Encoders/P1_MOSI: J5.10, R10.2, U3.4 (I/O3)
/Encoders/P1_SCK: J5.8, R8.2, U3.1 (I/O1)
/Encoders/P2_CS: J5.5, R23.2, U4.6 (I/O4)
/Encoders/P2_MISO: J5.3, R21.2, U4.3 (I/O2)
/Encoders/P2_MOSI: J5.4, R22.2, U4.4 (I/O3)
/Encoders/P2_SCK: J5.2, R20.2, U4.1 (I/O1)
/SPI1_MISO: R5.1; also elsewhere on the board
/SPI1_MOSI: R6.1; also elsewhere on the board
/SPI1_SCK: R4.1; also elsewhere on the board
/SPI2_MISO: R9.1; also elsewhere on the board
/SPI2_MOSI: R10.1; also elsewhere on the board
/SPI2_SCK: R8.1; also elsewhere on the board
/SPI3_MISO: R21.1; also elsewhere on the board
/SPI3_MOSI: R22.1; also elsewhere on the board
/SPI3_SCK: R20.1; also elsewhere on the board
GND: C17.2, C30.2, J5.6, J5.12, U3.2 (GND), U4.2 (GND), U6.8 (GND), U6.10 (TEST), U6.17 (EP); also elsewhere on the board
unnamed: F1.1, J5.1
unnamed: F2.1, J5.7
unnamed: R7.2, U6.5 (CS)
unnamed: R5.2, U6.7 (MISO)
unnamed: R6.2, U6.4 (MOSI)
unnamed: R4.2, U6.12 (SCLK)

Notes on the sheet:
J5: 12-pin JST-PH port. Pins 1-6 = port 2 (SPI3), pins 7-12 = port 1 (SPI2); each 1 +3V, 2 SCK, 3 MISO, 4 MOSI, 5 CS, 6 GND. N12: port power via PTC fuses F1 (pin 1) and F2 (pin 7), 100 mA hold, 0805.
22R series resistors on SCK/MISO/MOSI/CS of all three interfaces. USBLC6-4SC6 ESD array on each external port.
Encoders: onboard MA702GQ on SPI1 (CS = PC6 / ENC1_CS). Port 1 = SPI2 (CS = PC7 / ENC2_CS). Port 2 = SPI3 (CS = PC8 / ENC3_CS).

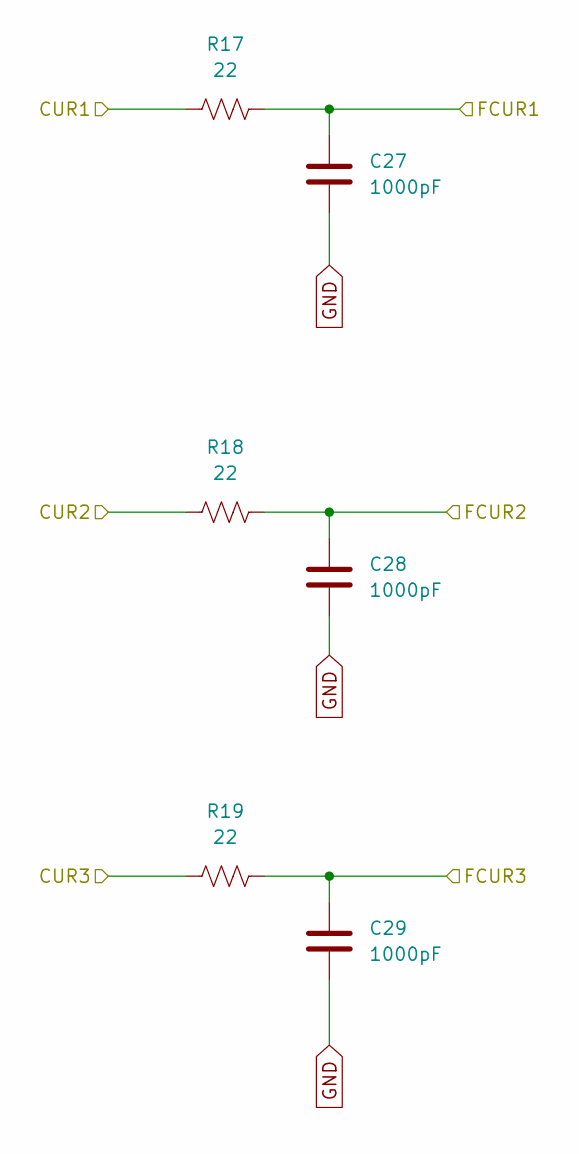
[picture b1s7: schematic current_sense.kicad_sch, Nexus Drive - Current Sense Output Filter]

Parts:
C27, C28, C29: 1000pF; C_0402_1005Metric; MPN MF-CAP-0402-1nF
R17, R18, R19: 22; R_0402_1005Metric; MPN MF-RES-0402-22

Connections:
/CUR1: R17.1; also elsewhere on the board
/CUR2: R18.1; also elsewhere on the board
/CUR3: R19.1; also elsewhere on the board
/CURR_A: C29.1, R19.2; also elsewhere on the board
/CURR_B: C28.1, R18.2; also elsewhere on the board
/CURR_C: C27.1, R17.2; also elsewhere on the board
GND: C27.2, C28.2, C29.2; also elsewhere on the board
